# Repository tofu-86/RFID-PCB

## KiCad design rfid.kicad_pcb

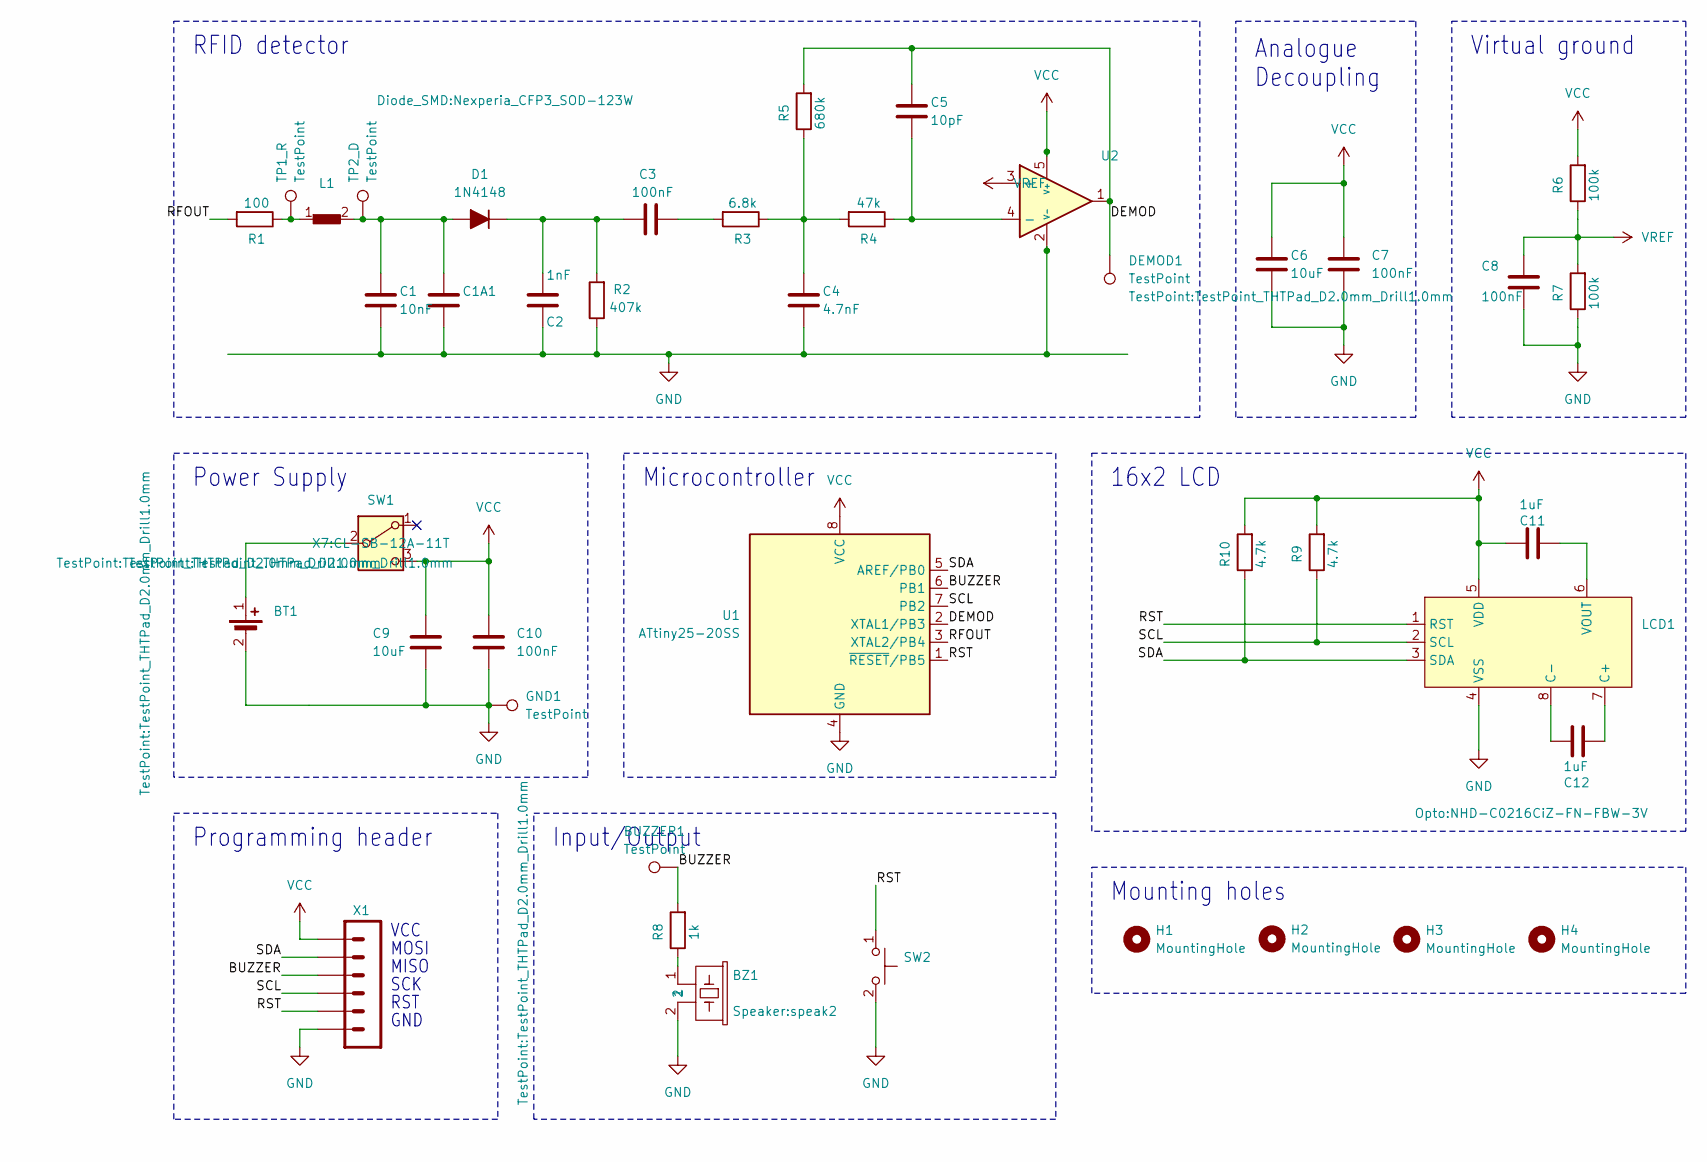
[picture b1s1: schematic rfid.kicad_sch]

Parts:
BT1: BatteryHolder_Keystone_3002_1x2032
BUZZER1: TestPoint; TestPoint_THTPad_D2.0mm_Drill1.0mm
BZ1: speak2
C1: 10nF; C_0603_1608Metric_Pad1.08x0.95mm_HandSolder
C1A1: C_0603_1608Metric_Pad1.08x0.95mm_HandSolder
C2: 1nF; C_0603_1608Metric_Pad1.08x0.95mm_HandSolder
C3, C7, C8, C10: 100nF; C_0603_1608Metric_Pad1.08x0.95mm_HandSolder
C4: 4.7nF; C_0603_1608Metric_Pad1.08x0.95mm_HandSolder
C5: 10pF; C_0603_1608Metric_Pad1.08x0.95mm_HandSolder
C6, C9: 10uF; C_0603_1608Metric_Pad1.08x0.95mm_HandSolder
C11, C12: 1uF; C_0603_1608Metric_Pad1.08x0.95mm_HandSolder
D1: 1N4148; Nexperia_CFP3_SOD-123W
DEMOD1: TestPoint; TestPoint_THTPad_D2.0mm_Drill1.0mm
GND1: TestPoint; TestPoint_THTPad_D2.0mm_Drill1.0mm
H1, H2, H3, H4: MountingHole; MountingHole_3mm_Pad
L1: COIL
LCD1: NHD-C0216CiZ-FN-FBW-3V
R1: 100; R_0603_1608Metric_Pad0.98x0.95mm_HandSolder
R2: 407k; R_0603_1608Metric_Pad0.98x0.95mm_HandSolder
R3: 6.8k; R_0603_1608Metric_Pad0.98x0.95mm_HandSolder
R4: 47k; R_0603_1608Metric_Pad0.98x0.95mm_HandSolder
R5: 680k; R_0603_1608Metric_Pad0.98x0.95mm_HandSolder
R6, R7: 100k; R_0603_1608Metric_Pad0.98x0.95mm_HandSolder
R8: 1k; R_0603_1608Metric_Pad0.98x0.95mm_HandSolder
R9, R10: 4.7k; R_0603_1608Metric_Pad0.98x0.95mm_HandSolder
SW1: CL-SB-12A-11T
SW2: 1571262-1
TP1_R, TP2_D: TestPoint; TestPoint_THTPad_D2.0mm_Drill1.0mm
U1: ATtiny25-20SS; SOIC-8_3.9x4.9mm_P1.27mm
U2: SOT-23-5_HandSoldering
X1: MH06-1-SMD

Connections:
/BUZZER: BUZZER1.1, R8.2, U1.6 (PB1), X1.3
/DEMOD: C5.1, DEMOD1.1, R5.2, U1.2 (XTAL1/PB3), U2.1
/RFOUT: R1.2, U1.3 (XTAL2/PB4)
/RST: LCD1.1 (RST), SW2.1, U1.1 (~RESET/PB5), X1.5
/SCL: LCD1.2 (SCL), R9.1, U1.7 (PB2), X1.4
/SDA: LCD1.3 (SDA), R10.1, U1.5 (AREF/PB0), X1.2
GND: BT1.2, BZ1.2, C1.2, C1A1.2, C2.1, C4.2, C6.2, C7.2, C8.2, C9.2, C10.2, GND1.1, LCD1.4 (VSS), R2.1, R7.1, SW2.2, U1.4 (GND), U2.2 (V-), X1.6
unnamed: BT1.1, SW1.2
unnamed: BZ1.1, R8.1
unnamed: C3.2, R3.2
unnamed: C4.1, R3.1, R4.2, R5.1
unnamed 11: C1.1, C1A1.1, D1.2 (A), L1.2, TP2_D.1; also elsewhere on the board
unnamed: C2.2, C3.1, D1.1 (K), R2.2
unnamed 13: L1.1, R1.1, TP1_R.1; also elsewhere on the board
unnamed: C12.2, LCD1.7 (C+)
unnamed: C12.1, LCD1.8 (C-)
unnamed: C11.2, LCD1.6 (VOUT)
unnamed: C5.2, R4.1, U2.4 (-)
VCC: C6.1, C7.1, C9.1, C10.1, C11.1, LCD1.5 (VDD), R6.2, R9.2, R10.2, SW1.3, U1.8 (VCC), U2.5 (V+), X1.1
VREF: C8.1, R6.1, R7.2, U2.3 (+)

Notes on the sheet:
MOSI
RST
MISO
16x2 LCD
VCC
RFID detector
Programming header
Microcontroller
Analogue Decoupling
Power Supply
GND
Virtual ground
SCK
Input/Output
Mounting holes

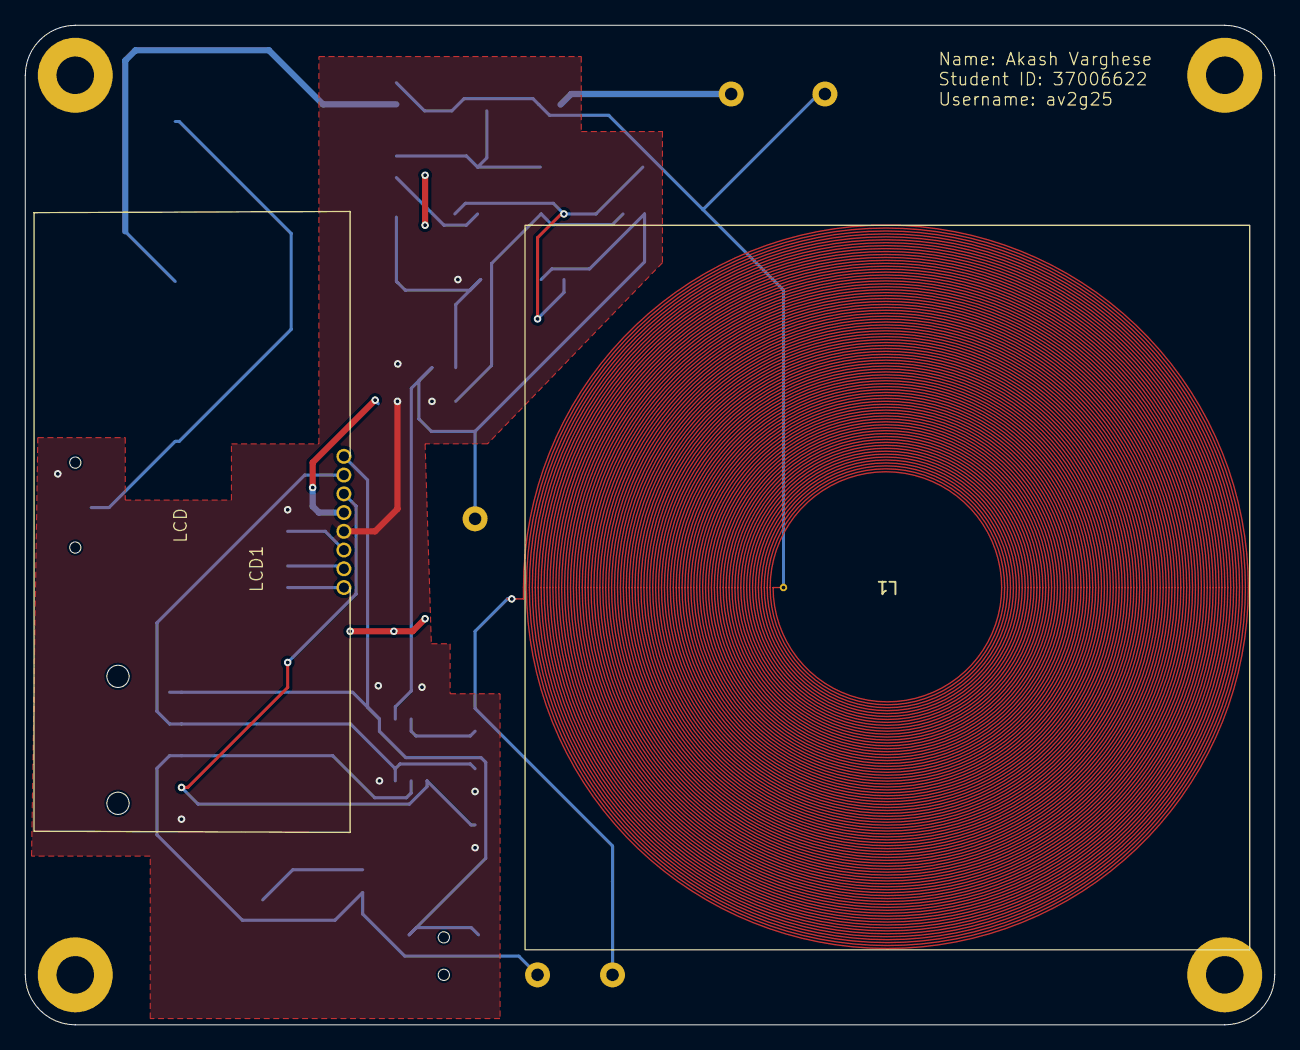
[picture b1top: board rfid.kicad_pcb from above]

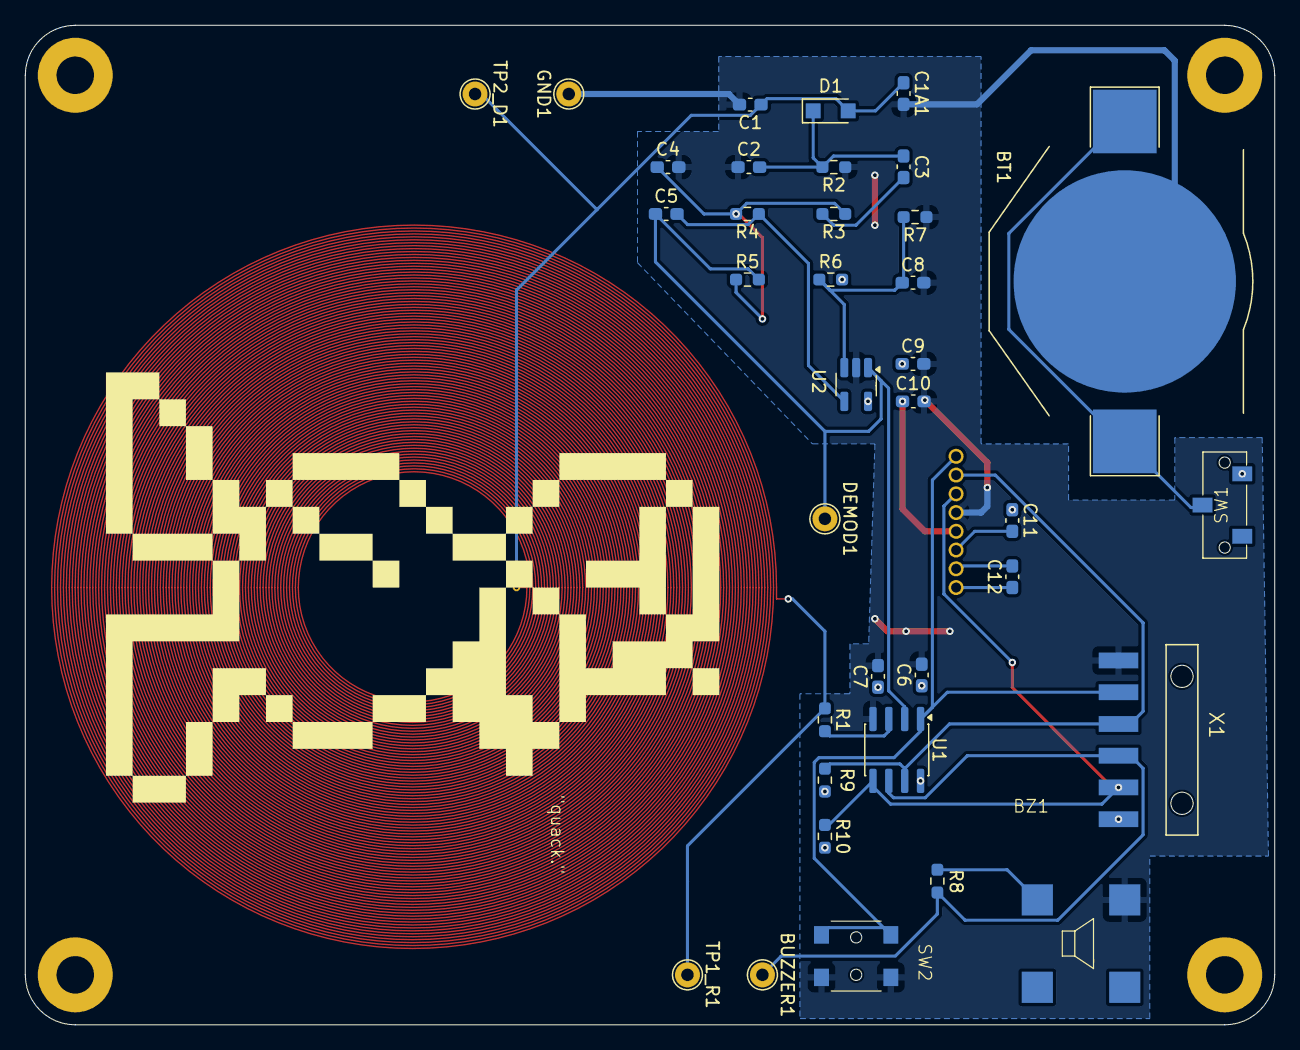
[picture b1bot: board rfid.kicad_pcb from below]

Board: 2 copper layers, 100.0 x 80.0 mm, 43 parts (37 on the bottom side), 20 nets.

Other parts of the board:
TP1_R1, TP2_D1: TestPoint; TestPoint_THTPad_D2.0mm_Drill1.0mm
quack: LOGO

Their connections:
unnamed 11: TP2_D1.1; also elsewhere on the board
unnamed 13: TP1_R1.1; also elsewhere on the board

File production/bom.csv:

Designator,Footprint,Quantity,Value,LCSC Part #
BT1,BatteryHolder_Keystone_3002_1x2032,1,~,
BZ1,speak2,1,~,
C1,0603,1,10nF,
"C10, C3, C7, C8",0603,4,100nF,
"C11, C12",0603,2,1uF,
C1A1,0603,1,~,
C2,0603,1,1nF,
C4,0603,1,4.7nF,
C5,0603,1,10pF,
"C6, C9",0603,2,10uF,
D1,Nexperia_CFP3_SOD-123W,1,1N4148,
LCD1,NHD-C0216CiZ-FN-FBW-3V,1,~,
R1,0603,1,100,
"R10, R9",0603,2,4.7k,
R2,0603,1,407k,
R3,0603,1,6.8k,
R4,0603,1,47k,
R5,0603,1,680k,
"R6, R7",0603,2,100k,
R8,0603,1,1k,
SW1,PowerSwitch,1,~,
SW2,1571262-1,1,~,
U1,SOIC-8_3.9x4.9mm_P1.27mm,1,ATtiny25-20SS,
U2,SOT-23-5_HandSoldering,1,~,
X1,MH06-1-SMD,1,~,

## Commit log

2026-02-13 initial
2026-02-22 New version
2026-02-22 inductor
2026-02-22 idek
2026-02-23 FInal
2026-02-23 finalv2
